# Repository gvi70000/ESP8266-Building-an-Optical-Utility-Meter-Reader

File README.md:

# ESP8266-Building-an-Optical-Utility-Meter-Reader

Introduction:

In the era of smart homes and energy efficiency, monitoring and managing your utility consumption has become a key aspect of modern living.

This article introduces a DIY project that combines new technology with a user-friendly approach, presenting an Optical Utility Meter Reader based on the ESP8266 microcontroller, BPW34 photodiode, and OPA2348/OPA2354 operational amplifier.

This intelligent device not only counts LED pulses from your utility meter but also seamlessly connects to your home network via WiFi and MQTT, offering a convenient and efficient way to integrate energy data into your smart home ecosystem.

This device will work only with utility meters that have a LED to indicate the consumption, for example my energy meter has a LED that blinks 1000time/kWh. It is marked on the meter as 1000 imp/kWh followed by a square pulse symbol = 1Wh.

Components and Technology:

ESP8266 for WiFi Connectivity: The ESP8266 is a powerful and cost-effective microcontroller with built-in WiFi capabilities. Leveraging its connectivity features, this Optical Utility Meter ensures seamless communication with your home network, allowing you to access real-time energy data from anywhere.

BPW34 Photodiode for Precision Sensing: The BPW34 photodiode serves as the optical sensor in the meter. Its high sensitivity to light ensures accurate counting of LED pulses from your utility meter. This precision is crucial for providing reliable energy consumption data, allowing you to make informed decisions about your usage patterns.

OPA2348/OPA2354 Op-Amp as a Schmidt Trigger: The OPA2348/2354 op-amp is utilized as a Schmidt trigger, helping to shape and stabilize the incoming signal from the photodiode. This ensures that the ESP8266 receives a clean and well-defined signal for processing, enhancing the overall reliability and accuracy of the meter.

MQTT Integration for Smart Home Connectivity: MQTT (Message Queuing Telemetry Transport) is a lightweight and efficient messaging protocol ideal for IoT devices. The Optical Utility Meter employs MQTT to transmit the pulse count data to a designated MQTT broker. This data can then be easily integrated into your smart home system, providing a comprehensive overview of your energy consumption.

Building the Optical Utility Meter Reader: The construction of this device involves connecting the components, programming the ESP8266 to handle the incoming data, and setting up the MQTT communication. Detailed step-by-step instructions and code snippets will be provided to guide you through the process, making it accessible to both beginners and experienced DIY enthusiasts.

The KiCAD schematic and PCB are provided in order to change them if you feel the need and also to make the understanding of the circuit easier.

The R2 value can be changed depending on the ambient light conditions, the larger it is the larger the voltage at the op-amp, I am using a 1MOhm resistor for R2.

The threshold voltage is set by the voltage divider formed by R10 and R11, I have used 470Ohm for R10 and 10kOhm for R11 to get a trigger voltage of 3.15V and also to be able to keep IO3 of the ESP high at boot.

With the values stated above I can read 1000pulses/sec from a 3mm red led 2cm away from photodiode.

The ESP8266 shall be connect with the VCC pin to the + on the PCB and GND to the - on the PCB. UART is not used so you can also use Receive and Transmit pins as you like.

I have attached also the stl files to 3D print the enclosure parts are: Upper cover and Lower Cover. You will need a small self tapping screw with a diameter smaller than 2mm to fix the PCB in the Lower cover. The Upper Cover, after the power cable is connected through the hole, can be glued in place.

Double sided adhesive tape is used to fix the assembled enclosure on the meter.

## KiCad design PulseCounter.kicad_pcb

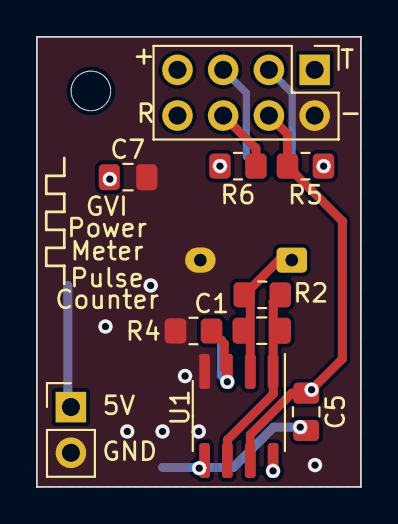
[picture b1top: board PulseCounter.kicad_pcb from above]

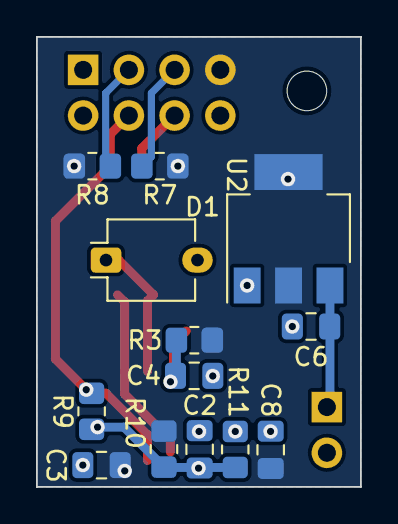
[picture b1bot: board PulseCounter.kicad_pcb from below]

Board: 2 copper layers, 18.0 x 25.0 mm, 24 parts (13 on the bottom side), 11 nets.

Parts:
C1: 4.7n; C_0805_2012Metric_Pad1.18x1.45mm_HandSolder
C2, C7: 10u; C_0805_2012Metric_Pad1.18x1.45mm_HandSolder
C3: 1u; C_0805_2012Metric_Pad1.18x1.45mm_HandSolder
C4: 4.7u; C_0805_2012Metric_Pad1.18x1.45mm_HandSolder
C5: 100p; C_0805_2012Metric_Pad1.18x1.45mm_HandSolder
C6, C8: 100n; C_0805_2012Metric_Pad1.18x1.45mm_HandSolder
D1: BPW34; Osram_DIL2_4.3x4.65mm_P5.08mm
ESP1: Conn_02x04_Odd_Even; PinHeader_2x04_P2.54mm_Vertical
H1: MountingHole; MountingHole_2.2mm_M2_DIN965
J1: Conn_01x02; PinHeader_1x02_P2.54mm_Vertical
R2: 330k; R_0805_2012Metric_Pad1.20x1.40mm_HandSolder
R3: 100k; R_0805_2012Metric_Pad1.20x1.40mm_HandSolder
R4, R5, R6, R7, R8, R11: 10k; R_0805_2012Metric_Pad1.20x1.40mm_HandSolder
R9: 47k; R_0805_2012Metric_Pad1.20x1.40mm_HandSolder
R10: 22k; R_0805_2012Metric_Pad1.20x1.40mm_HandSolder
U1: OPA2354; SOIC-8_3.9x4.9mm_P1.27mm
U2: AP1117-33; SOT-223-3_TabPin2

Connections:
+3V3: C3.1, C7.1, C8.1, ESP1.7, R3.2, R5.2, R6.2, R7.2, R8.2, R10.2, U1.8 (V+), U2.2 (VO)
+5V: C6.1, J1.1, U2.3 (VI)
ESP_RST: ESP1.5, R7.1
GND: C2.2, C3.2, C4.2, C6.2, C7.2, C8.2, D1.2 (A), ESP1.2, J1.2, R4.1, R11.1, U1.4 (V-), U2.1 (GND)
IO0: ESP1.6, R6.1
IO2: C5.2, ESP1.4, R5.1, R9.2, U1.7
unnamed: C1.2, D1.1 (K), R2.1, U1.2 (-)
unnamed: ESP1.3, R8.1
unnamed: C1.1, R2.2, U1.1, U1.6 (-)
V_BIAS: C4.1, R3.1, R4.2, U1.3 (+)
V_TRIGG: C2.1, C5.1, R9.1, R10.1, R11.2, U1.5 (+)

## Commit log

2024-02-25 LatestVersion
